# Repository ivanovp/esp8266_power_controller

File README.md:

# esp8266_power_controller
ESP8266 wireless sensor and power controller with P1 (smart meter) input

Videos about the controller (currently only in Hungarian).

Introduction:
https://youtu.be/gTx1W5xfqio

Explaining schematic and PCB:
https://youtu.be/oL1xu2TVqEM

How to configure and upload software:
https://youtu.be/lelAveujqwc

Designing 3D printable case:
https://youtu.be/UKCy7zpQ2Bw

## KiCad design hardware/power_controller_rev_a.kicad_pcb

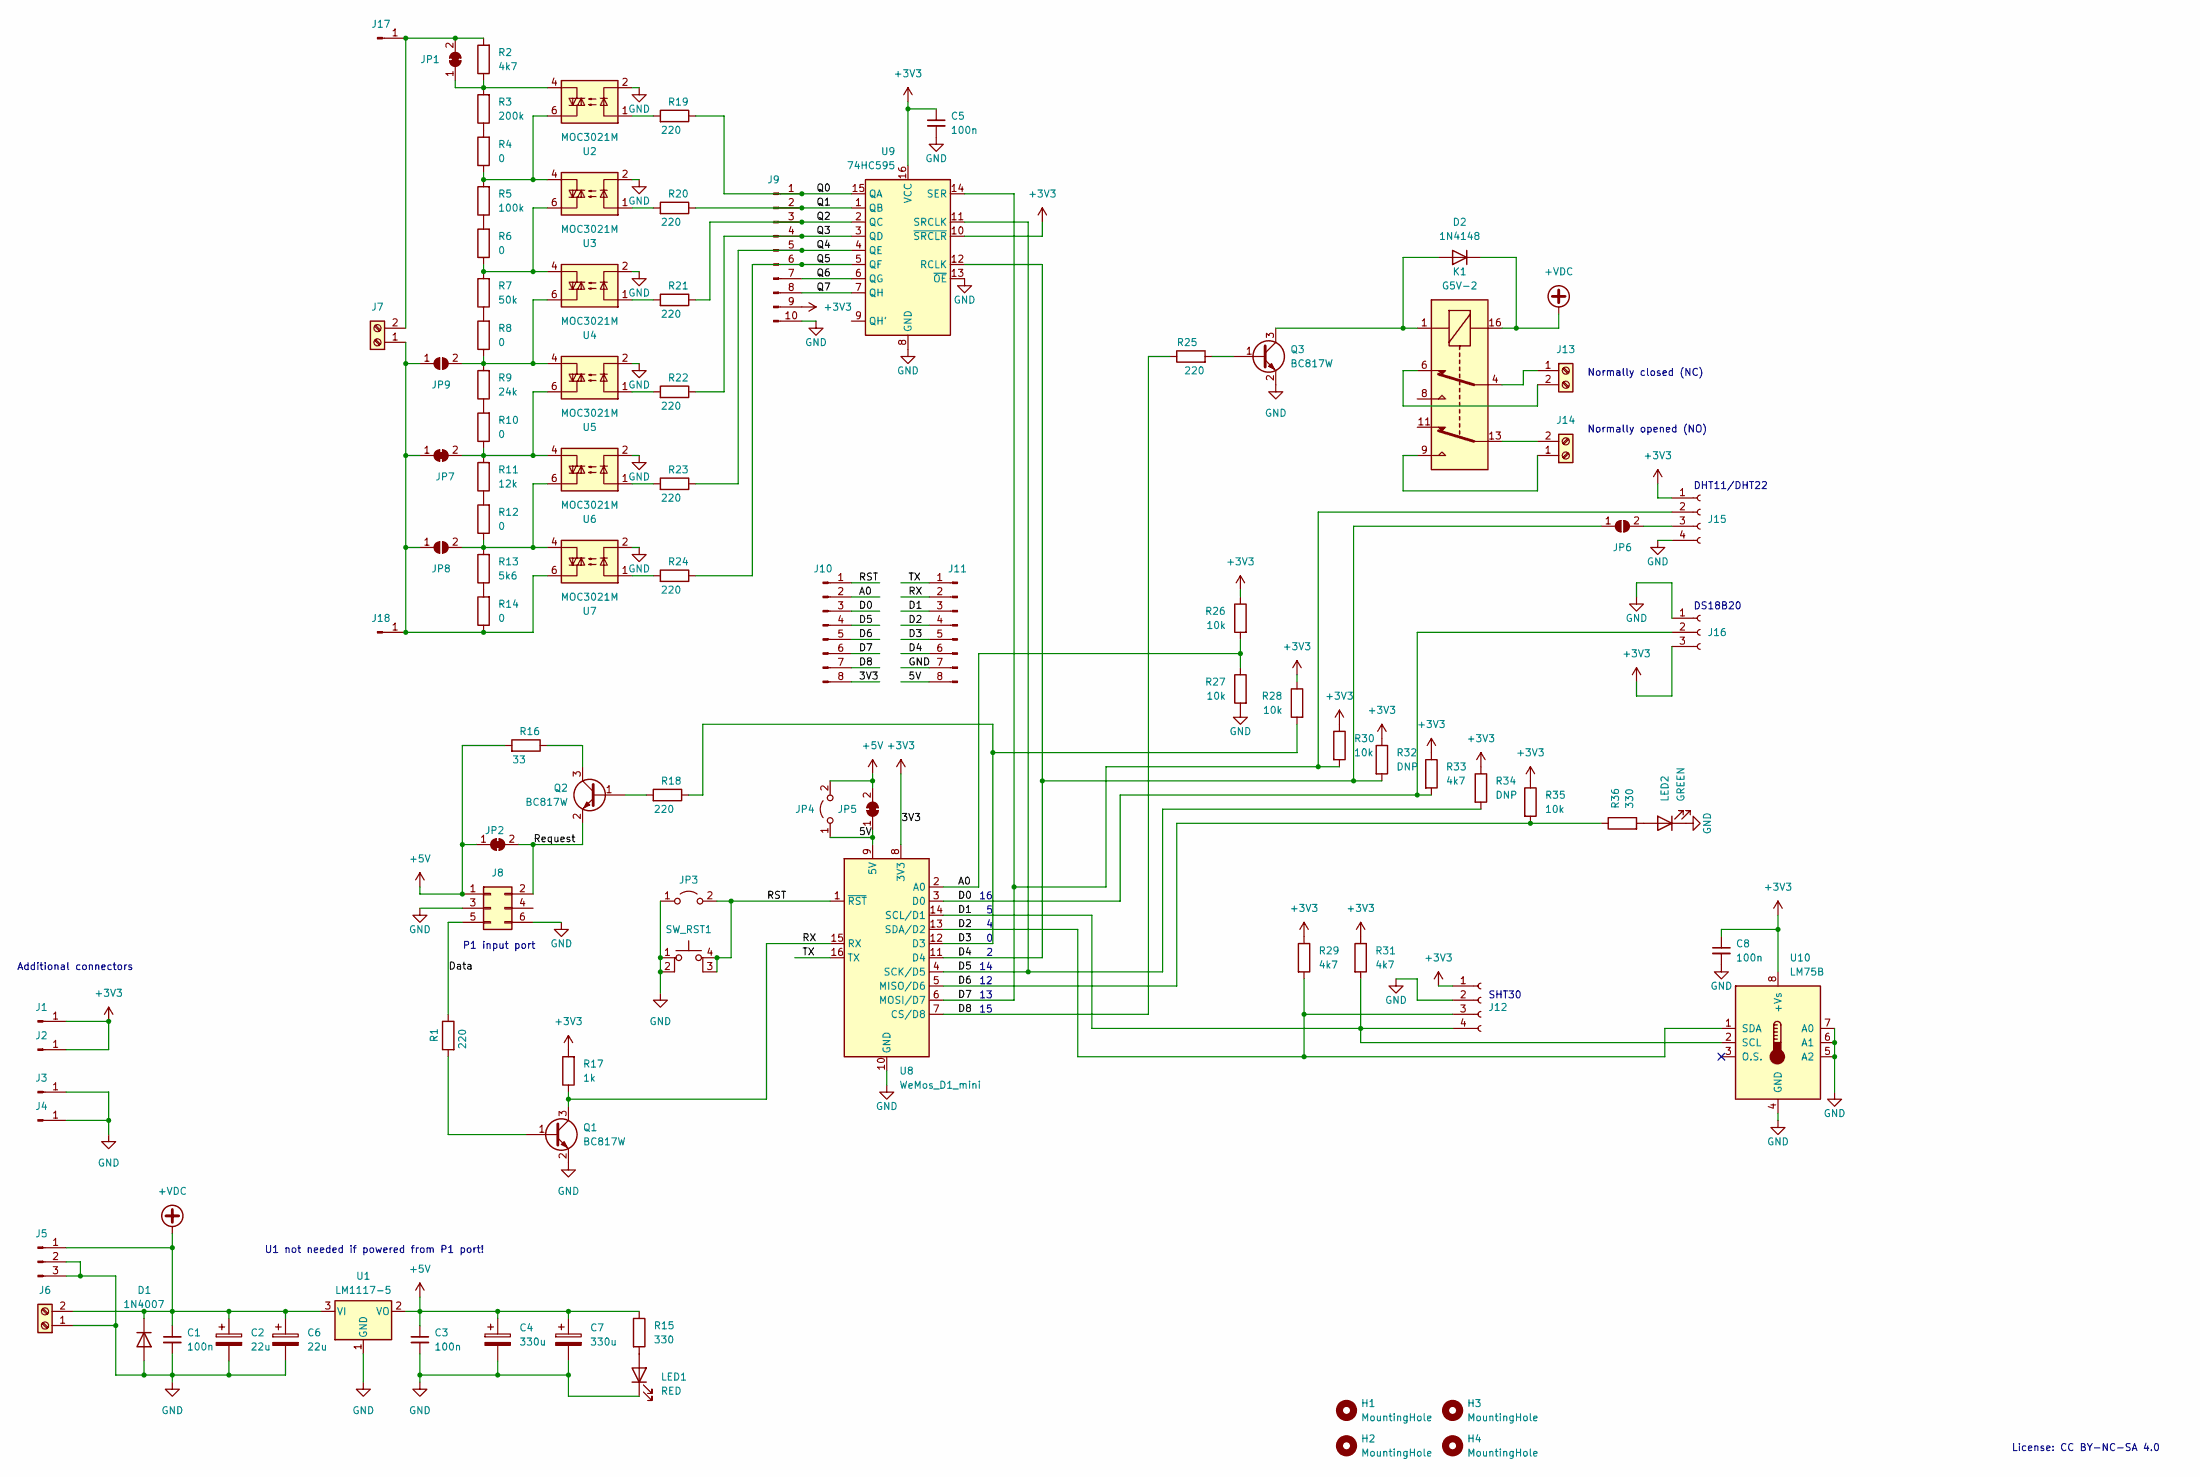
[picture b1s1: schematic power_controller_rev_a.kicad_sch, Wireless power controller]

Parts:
C1, C3, C5, C8: 100n; C_0805_2012Metric_Pad1.18x1.45mm_HandSolder
C2: 22u; CP_Radial_D6.3mm_P2.50mm
C4: 330u; CP_Radial_D6.3mm_P2.50mm
C6: 22u; CP_Elec_4x3.9
C7: 330u; CP_Elec_4x3.9
D1: 1N4007; D_DO-41_SOD81_P10.16mm_Horizontal
D2: 1N4148; D_DO-35_SOD27_P7.62mm_Horizontal
H1, H2, H3, H4: MountingHole; MountingHole_3.2mm_M3_DIN965
J1, J2, J3, J4, J17, J18: Conn_01x01_Male; PinHeader_1x01_P2.54mm_Vertical
J5: Conn_01x03_Male; PinHeader_1x03_P2.54mm_Vertical
J6, J7, J13, J14: Screw_Terminal_01x02; TerminalBlock_Phoenix_MKDS-1,5-2-5.08_1x02_P5.08mm_Horizont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
J8: Conn_02x03_Odd_Even; PinHeader_2x03_P2.54mm_Horizontal
J9: Conn_01x10_Pin; PinHeader_1x10_P2.54mm_Vertical
J10, J11: Conn_01x08_Pin; PinHeader_1x08_P2.54mm_Vertical
J12, J15: Conn_01x04_Female; PinSocket_1x04_P2.54mm_Vertical
J16: Conn_01x03_Female; PinSocket_1x03_P2.54mm_Vertical
JP1, JP2, JP5, JP7: SolderJumper_2_Bridged; SolderJumper-2_P1.3mm_Bridged_Pad1.0x1.5mm
JP3, JP4: Jumper_2_Open; TestPoint_2Pads_Pitch2.54mm_Drill0.8mm
JP6, JP8, JP9: SolderJumper_2_Open; SolderJumper-2_P1.3mm_Open_Pad1.0x1.5mm
K1: G5V-2; Relay_DPDT_Omron_G5V-2
LED1: RED; LED_0805_1206_3216Metric_Pad1.42x1.75mm_HandSolder
LED2: GREEN; LED_0805_1206_3216Metric_Pad1.42x1.75mm_HandSolder
Q1, Q2, Q3: BC817W; SOT-323_SC-70
R1, R18, R19, R20, R21, R22, R23, R24, R25: 220; R_0805_2012Metric_Pad1.20x1.40mm_HandSolder
R2: 4k7; R_Axial_DIN0207_L6.3mm_D2.5mm_P7.62mm_Horizontal
R3: 200k; R_Axial_DIN0207_L6.3mm_D2.5mm_P2.54mm_Vertical
R4, R6, R8, R10, R12, R14: 0; R_Axial_DIN0207_L6.3mm_D2.5mm_P2.54mm_Vertical
R5: 100k; R_Axial_DIN0207_L6.3mm_D2.5mm_P2.54mm_Vertical
R7: 50k; R_Axial_DIN0207_L6.3mm_D2.5mm_P2.54mm_Vertical
R9: 24k; R_Axial_DIN0207_L6.3mm_D2.5mm_P2.54mm_Vertical
R11: 12k; R_Axial_DIN0207_L6.3mm_D2.5mm_P2.54mm_Vertical
R13: 5k6; R_Axial_DIN0207_L6.3mm_D2.5mm_P2.54mm_Vertical
R15, R36: 330; R_0805_2012Metric_Pad1.20x1.40mm_HandSolder
R16: 33; R_0805_2012Metric_Pad1.20x1.40mm_HandSolder
R17: 1k; R_0805_2012Metric_Pad1.20x1.40mm_HandSolder
R26, R27, R28, R30, R35: 10k; R_0805_2012Metric_Pad1.20x1.40mm_HandSolder
R29, R31, R33: 4k7; R_0805_2012Metric_Pad1.20x1.40mm_HandSolder
R32, R34: DNP; R_0805_2012Metric_Pad1.20x1.40mm_HandSolder
SW_RST1: SW_MEC_5E; SW_TH_Tactile_Omron_B3F-10xx
U1: LM1117-5; SOT-223-3_TabPin2
U2, U3, U4, U5, U6, U7: MOC3021M; DIP-6_W7.62mm
U8: WeMos_D1_mini; WEMOS_D1_mini_light
U9: 74HC595; SOIC-16_3.9x9.9mm_P1.27mm
U10: LM75B; SOIC-8_3.9x4.9mm_P1.27mm

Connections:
+3V3: C5.1, C8.1, J1.1, J2.1, J9.9, J10.8, J12.1, J15.1, J16.3, R17.2, R26.1, R28.1, R29.1, R30.1, R31.1, R32.1, R33.1, R34.1, R35.1, U8.8 (3V3), U9.10 (~SRCLR), U9.16 (VCC), U10.8 (+Vs)
+5V: C3.1, C4.1, C7.1, J8.1, JP2.1 (A), JP4.2 (B), JP5.2 (B), R15.1, R16.2, U1.2 (VO)
+VDC: C1.1, C2.1, C6.1, D1.1 (K), D2.1 (K), J5.1, J6.2, K1.16, U1.3 (VI)
/5V: J11.8, JP4.1 (A), JP5.1 (A), U8.9 (5V)
/A0: J10.2, R26.2, R27.1, U8.2 (A0)
/D0: J10.3, J16.2, R33.2, U8.3 (D0)
/D1: J11.3, J12.4, R31.2, U8.14 (SCL/D1), U10.2 (SCL)
/D2: J11.4, J12.3, R29.2, U8.13 (SDA/D2), U10.1 (SDA)
/D3: J11.5, R18.1, R28.2, U8.12 (D3)
/D4: J11.6, JP6.1 (A), R32.2, U8.11 (D4), U9.12 (RCLK)
/D5: J10.4, R34.2, U8.4 (SCK/D5), U9.11 (SRCLK)
/D6: J10.5, R35.2, R36.1, U8.5 (MISO/D6)
/D7: J10.6, J15.2, R30.2, U8.6 (MOSI/D7), U9.14 (SER)
/D8: J10.7, R25.1, U8.7 (CS/D8)
/Data: J8.5, R1.1
/Q0: J9.1, R19.1, U9.15 (QA)
/Q1: J9.2, R20.1, U9.1 (QB)
/Q2: J9.3, R21.1, U9.2 (QC)
/Q3: J9.4, R22.1, U9.3 (QD)
/Q4: J9.5, R23.1, U9.4 (QE)
/Q5: J9.6, R24.1, U9.5 (QF)
/Q6: J9.7, U9.6 (QG)
/Q7: J9.8, U9.7 (QH)
/RST: J10.1, JP3.2 (B), SW_RST1.3 (K), SW_RST1.4 (A), U8.1 (~RST)
/RX: J11.2, Q1.3 (C), R17.1, U8.15 (RX)
/Request: J8.2, JP2.2 (B), Q2.2 (E)
/TX: J11.1, U8.16 (TX)
GND: C1.2, C2.2, C3.2, C4.2, C5.2, C6.2, C7.2, C8.2, D1.2 (A), J3.1, J4.1, J5.2, J5.3, J6.1, J8.3, J8.6, J9.10, J11.7, J12.2, J15.4, J16.1, JP3.1 (A), LED1.1 (K), LED2.1 (K), Q1.2 (E), Q3.2 (E), R27.2, SW_RST1.1, SW_RST1.2, U1.1 (GND), U2.2, U3.2, U4.2, U5.2, U6.2, U7.2, U8.10 (GND), U9.8 (GND), U9.13 (~OE), U10.4 (GND), U10.5 (A2), U10.6 (A1), U10.7 (A0)
unnamed: D2.2 (A), K1.1, Q3.3 (C)
unnamed: J13.1, K1.4
unnamed: J13.2, K1.6
unnamed: J14.1, K1.9
unnamed: J14.2, K1.13
unnamed: J15.3, JP6.2 (B)
unnamed: J7.2, J17.1, JP1.2 (B), R2.2
unnamed: J7.1, J18.1, JP7.1 (A), JP8.1 (A), JP9.1 (A), R14.1, U7.6
unnamed: JP1.1 (A), R2.1, R3.2, U2.4
unnamed: JP7.2 (B), R10.1, R11.2, U5.6, U6.4
unnamed: JP8.2 (B), R12.1, R13.2, U6.6, U7.4
unnamed: JP9.2 (B), R8.1, R9.2, U4.6, U5.4
unnamed: LED1.2 (A), R15.2
unnamed: LED2.2 (A), R36.2
unnamed: Q1.1 (B), R1.2
unnamed: Q2.1 (B), R18.2
unnamed: Q2.3 (C), R16.1
unnamed: Q3.1 (B), R25.2
unnamed: R3.1, R4.2
unnamed: R4.1, R5.2, U2.6, U3.4
unnamed: R5.1, R6.2
unnamed: R6.1, R7.2, U3.6, U4.4
unnamed: R7.1, R8.2
unnamed: R9.1, R10.2
unnamed: R11.1, R12.2
unnamed: R13.1, R14.2
unnamed: R19.2, U2.1
unnamed: R20.2, U3.1
unnamed: R21.2, U4.1
unnamed: R22.2, U5.1
unnamed: R23.2, U6.1
unnamed: R24.2, U7.1

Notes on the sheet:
P1 input port
License: CC BY-NC-SA 4.0
Normally closed (NC)
DS18B20
U1 not needed if powered from P1 port!
DHT11/DHT22
SHT30
Normally opened (NO)
Additional connectors

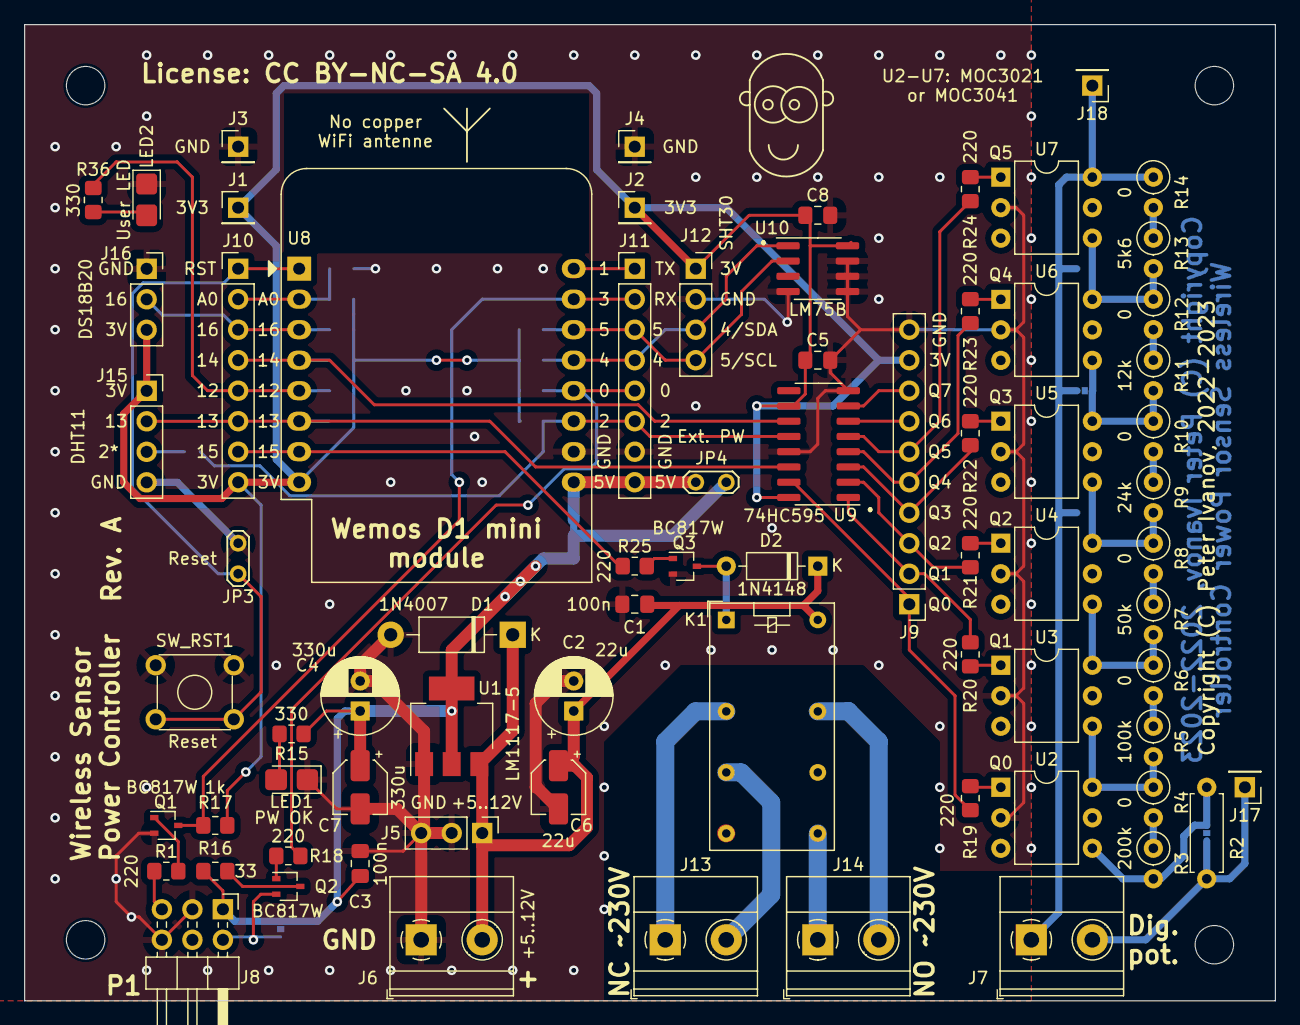
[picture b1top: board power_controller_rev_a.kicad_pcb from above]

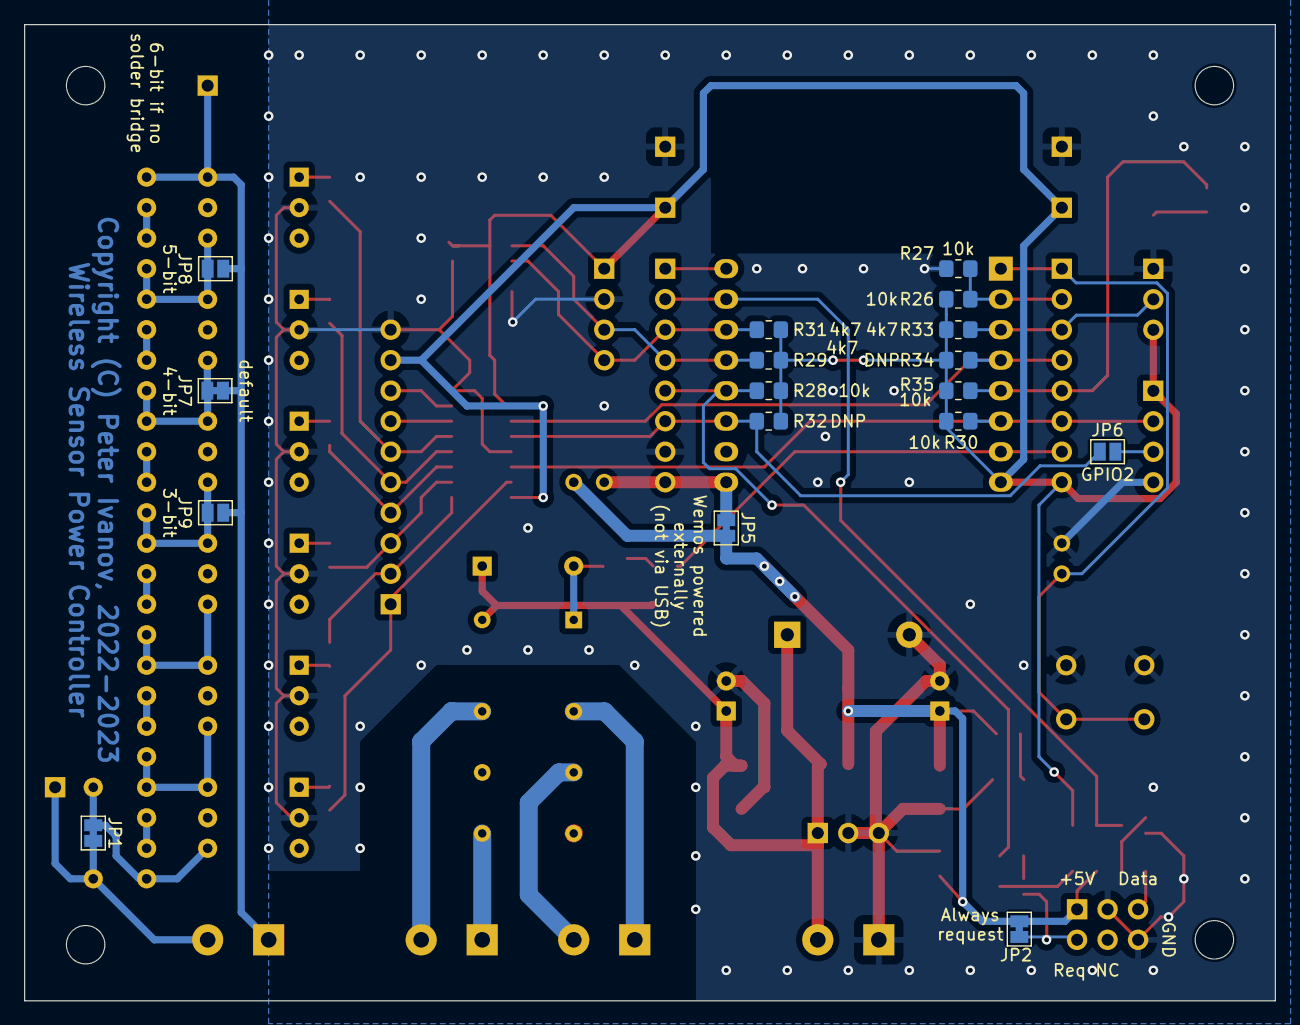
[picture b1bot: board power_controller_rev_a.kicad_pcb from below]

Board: 2 copper layers, 104.1 x 81.3 mm, 94 parts (17 on the bottom side), 60 nets.

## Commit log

2023-11-04 Initial commit of software.
2023-11-04 Initial commit of hardware.
2023-11-06 Images of power controller were added.
2023-11-06 Readme was updated.
2023-11-07 MQTT client can be disabled in config.h. Maximum current can be defined in digipot.txt.
2023-11-07 Typo was fixed in digipot.txt. Comment was added.
2023-11-09 Comments were added.
2023-11-13 Comments were added and fixed in configuration. Test buttons were disabled.
2023-11-13 Case was added: FreeCAD design and STL files.
2023-11-17 Picture of 3D printed case was added. Another youtube link was added to Readme.
2023-11-17 Picture of 3D printed case was added to Readme.
2023-11-19 Compiling error was eliminated which occurred when ENABLE_POWER_METER=0.
2025-01-24 MQTT username and password is used.

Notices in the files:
hardware/power_controller_rev_a.kicad_pcb:
Copyright (C) Peter Ivanov, 2022-2023
hardware/power_controller_rev_a.kicad_sch:
Copyright (C) Peter Ivanov , 2023
